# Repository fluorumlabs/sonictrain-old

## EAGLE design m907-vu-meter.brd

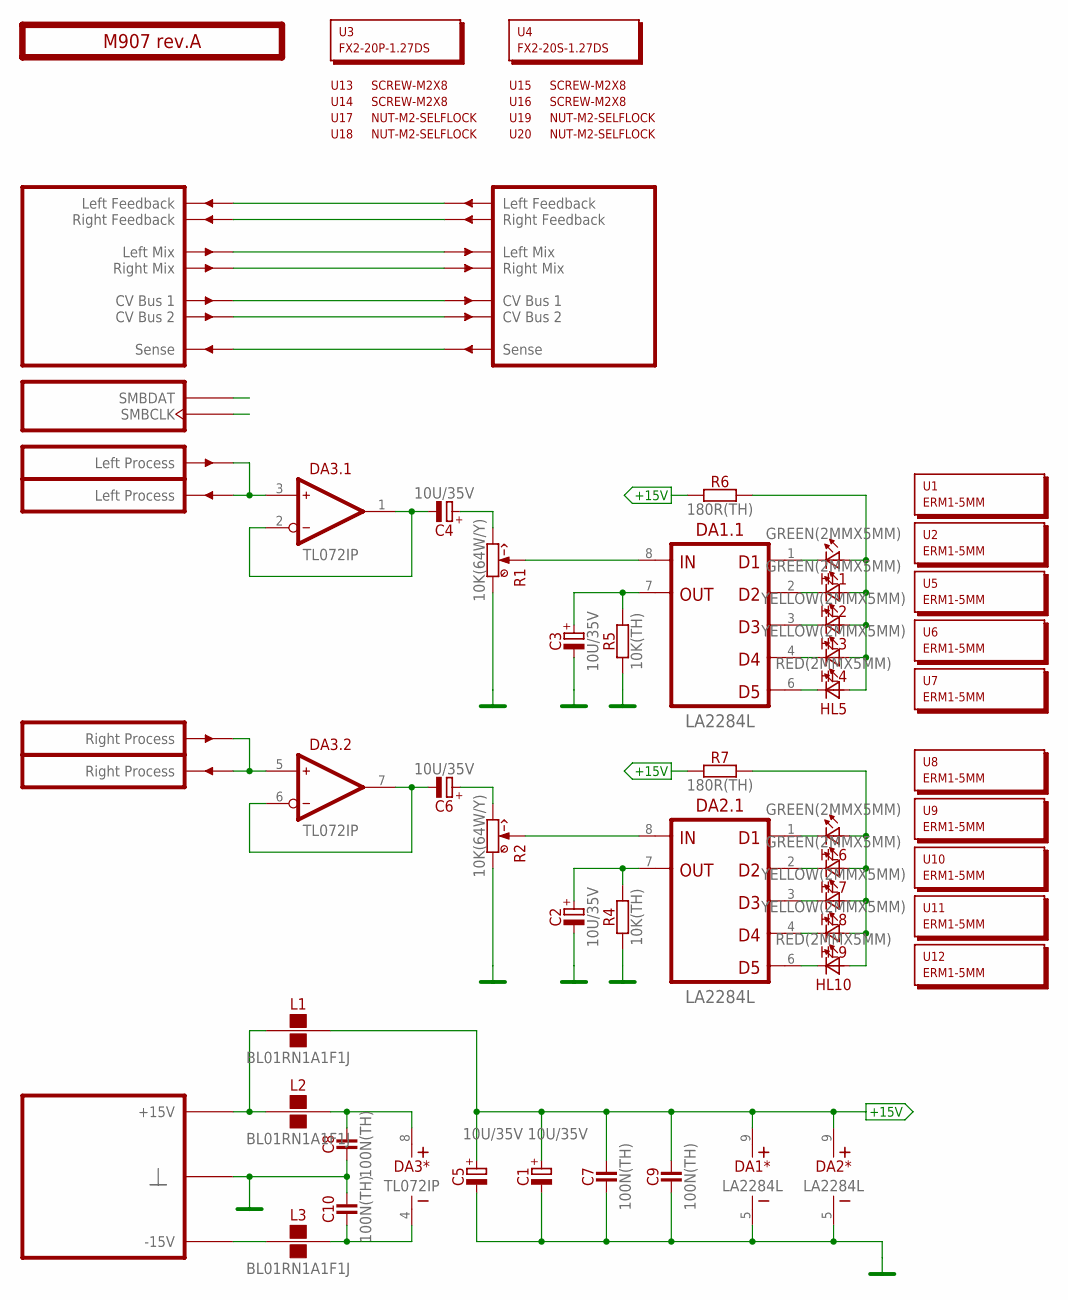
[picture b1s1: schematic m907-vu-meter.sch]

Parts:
C1, C2, C3, C4, C5, C6: 10U/35V; E2-5
C7, C8, C9, C10: 100N(TH); C050-024X044
DA1, DA2: LA2284L; SIL9
DA3: TL072IP; DIP-8
HL1, HL2, HL6, HL7: GREEN(2MMX5MM); LED2X5
HL3, HL4, HL8, HL9: YELLOW(2MMX5MM); LED2X5
HL5, HL10: RED(2MMX5MM); LED2X5
L1, L2, L3: BL01RN1A1F1J; BL01RN1A
PCB1: M907 rev.A; ST2-BOARD-26
R1, R2: 10K(64W/Y); 64W
R4, R5: 10K(TH); R-0207/10
R6, R7: 180R(TH); R-0207/10
U1, U2, U5, U6, U7, U8, U9, U10, U11, U12: ERM1-5MM; EMPTY
U3: FX2-20P-1.27DS; EMPTY
U4: FX2-20S-1.27DS; EMPTY
U13, U14, U15, U16: SCREW-M2X8; EMPTY
U17, U18, U19, U20: NUT-M2-SELFLOCK; EMPTY

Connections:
+15V: C1.+, C5.+, C7.2, C9.2, DA1.9 (V+), DA2.9 (V+), L1.2, R6.1, R7.1
GND: C1.-, C2.-, C3.-, C5.-, C7.1, C8.1, C9.1, C10.2, DA1.5 (V-), DA2.5 (V-), PCB1.B4 (GND), PCB1.B4' (GND), PCB1.B5 (GND), PCB1.B5' (GND), PCB1.B6 (GND), PCB1.B6' (GND), PCB1.B7 (GND), PCB1.B7' (GND), PCB1.B8 (GND), PCB1.B8' (GND), R1.1 (CCW), R2.1 (CCW), R4.1, R5.1
LMIX: PCB1.ALMIX (LMIX), PCB1.ALMIX' (LMIX')
unnamed: L1.1, L2.1, PCB1.A+15 (P+15V), PCB1.A+15' (P+15V), PCB1.B+15 (P+15V), PCB1.B+15' (P+15V)
unnamed: PCB1.ALFBK (LFBK), PCB1.ALFBK' (LFBK')
unnamed: DA2.8 (IN), R2.S (W), R2.S@1 (W)
unnamed: PCB1.ARFBK (RFBK), PCB1.ARFBK' (RFBK')
unnamed: DA1.8 (IN), R1.S (W), R1.S@1 (W)
unnamed: C3.+, DA1.7 (OUT), R5.2
unnamed: C2.+, DA2.7 (OUT), R4.2
unnamed: HL1.A, HL2.A, HL3.A, HL4.A, HL5.A, R6.2
unnamed: DA1.1 (D1), HL1.K (C)
unnamed: DA1.2 (D2), HL2.K (C)
unnamed: DA1.3 (D3), HL3.K (C)
unnamed: DA1.4 (D4), HL4.K (C)
unnamed: DA1.6 (D5), HL5.K (C)
unnamed: HL6.A, HL7.A, HL8.A, HL9.A, HL10.A, R7.2
unnamed: DA2.1 (D1), HL6.K (C)
unnamed: PCB1.BSENSE (SENSE), PCB1.BSENSE' (SENSE')
unnamed: DA2.2 (D2), HL7.K (C)
unnamed: DA2.3 (D3), HL8.K (C)
unnamed: DA2.4 (D4), HL9.K (C)
unnamed: DA2.6 (D5), HL10.K (C)
unnamed: C4.+, R1.3 (CW)
unnamed: C6.+, R2.3 (CW)
unnamed: DA3.3 (IN+), PCB1.BINL (INL), PCB1.BOUTL' (OUTL)
unnamed: DA3.5 (IN+), PCB1.BINR (INR), PCB1.BOUTR' (OUTR)
unnamed: L3.1, PCB1.A-15 (P-15V), PCB1.A-15' (P-15V), PCB1.B-15 (P-15V), PCB1.B-15' (P-15V)
unnamed: C8.2, DA3.8 (V+), L2.2
unnamed: C10.1, DA3.4 (V-), L3.2
unnamed: C4.-, DA3.1 (OUT), DA3.2 (IN-)
unnamed: C6.-, DA3.6 (IN-), DA3.7 (OUT)
unnamed: PCB1.ASMBDAT (SMBDAT), PCB1.ASMBDAT' (SMBDAT)
unnamed: PCB1.ACV1 (CV1), PCB1.ACV1' (CV1')
unnamed: PCB1.ACV2 (CV2), PCB1.ACV2' (CV2')
unnamed: PCB1.ASMBCLK (SMBCLK), PCB1.ASMBCLK' (SMBCLK)
RMIX: PCB1.ARMIX (RMIX), PCB1.ARMIX' (RMIX')

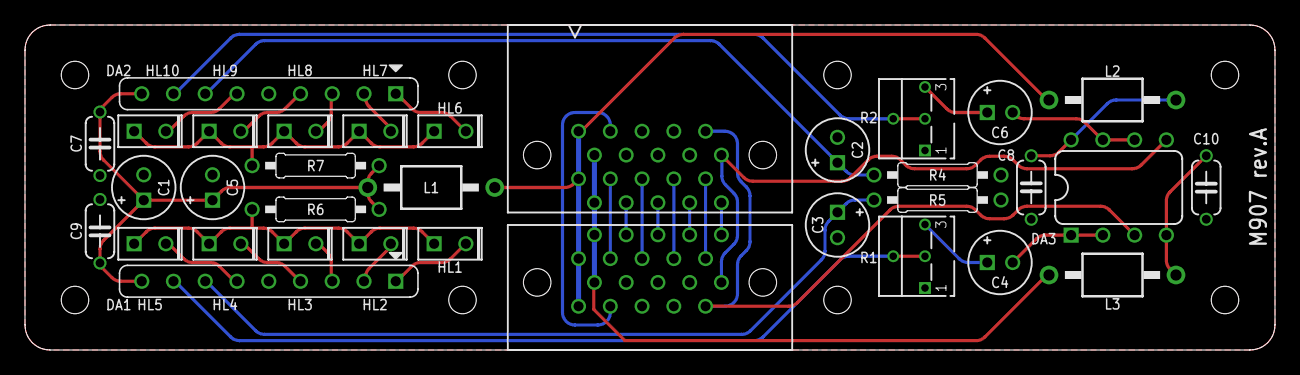
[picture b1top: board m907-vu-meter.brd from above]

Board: 2 copper layers, 100.0 x 26.0 mm, 53 parts (0 on the bottom side), 37 nets.

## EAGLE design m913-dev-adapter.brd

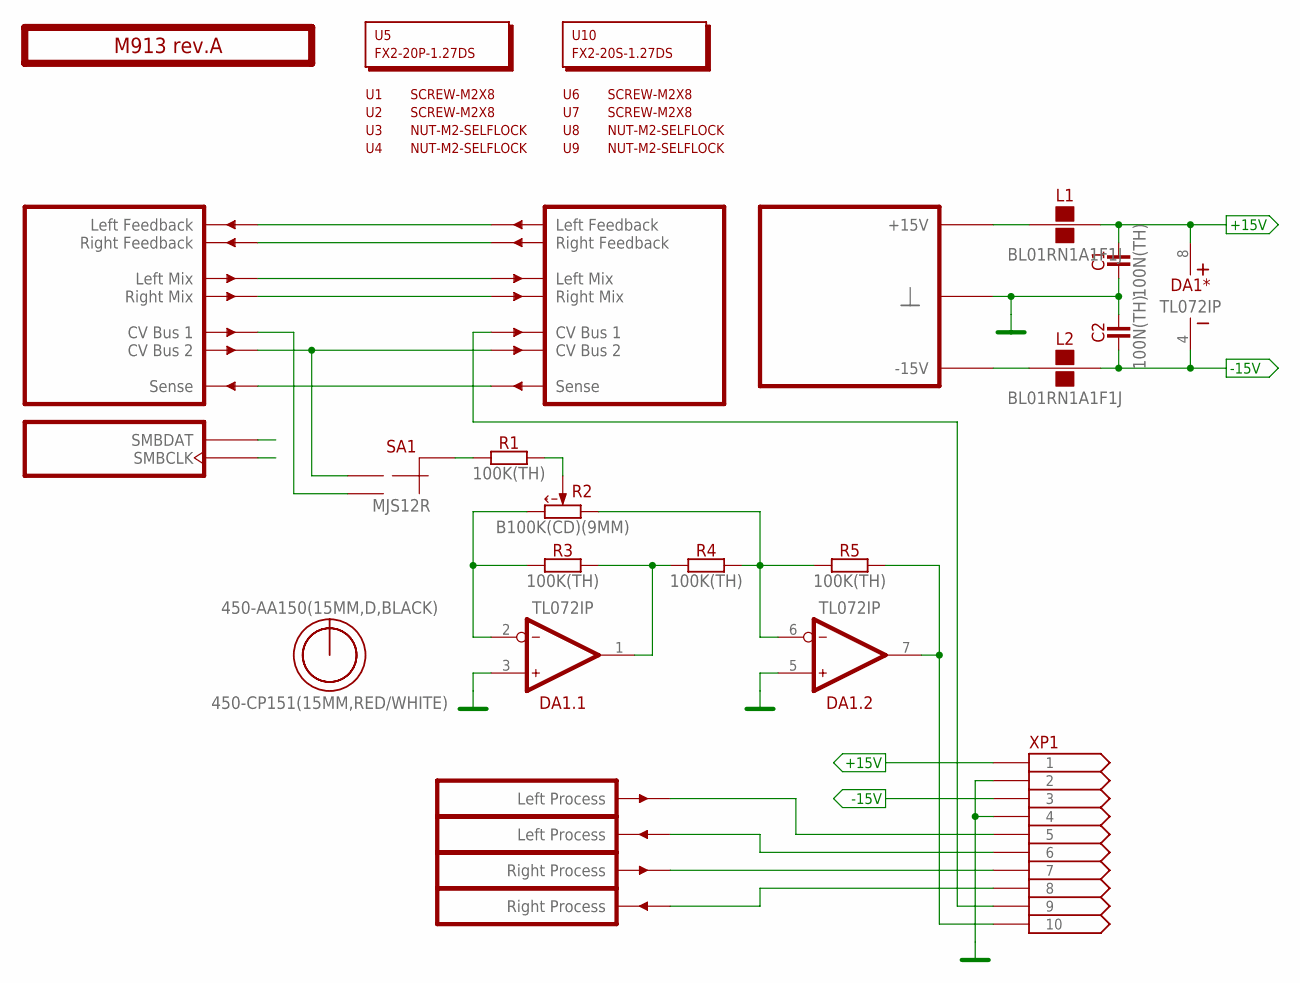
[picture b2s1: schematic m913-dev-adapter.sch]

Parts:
C1, C2: 100N(TH); C050-024X044
DA1: TL072IP; DIP-8
L1, L2: BL01RN1A1F1J; BL01RN1A
O1: 450-AA150(15MM,D,BLACK); EMPTY
O2: 450-CP151(15MM,RED/WHITE); EMPTY
PCB1: M913 rev.A; ST2-BOARD-26
R1, R3, R4, R5: 100K(TH); R-0207/10
R2: B100K(CD)(9MM); RV09-SINGLE
SA1: MJS12R; APEM-MJS12R
U1, U2, U6, U7: SCREW-M2X8; EMPTY
U3, U4, U8, U9: NUT-M2-SELFLOCK; EMPTY
U5: FX2-20P-1.27DS; EMPTY
U10: FX2-20S-1.27DS; EMPTY
XP1: CONN-10-IDC; ML10

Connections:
+15V: C1.2, DA1.8 (V+), L1.2, XP1.1
-15V: C2.1, DA1.4 (V-), L2.2, XP1.3
GND: C1.1, C2.2, DA1.3 (IN+), DA1.5 (IN+), PCB1.B4 (GND), PCB1.B4' (GND), PCB1.B5 (GND), PCB1.B5' (GND), PCB1.B6 (GND), PCB1.B6' (GND), PCB1.B7 (GND), PCB1.B7' (GND), PCB1.B8 (GND), PCB1.B8' (GND), XP1.2, XP1.4
LMIX: PCB1.ALMIX (LMIX), PCB1.ALMIX' (LMIX')
unnamed: L1.1, PCB1.A+15 (P+15V), PCB1.A+15' (P+15V), PCB1.B+15 (P+15V), PCB1.B+15' (P+15V)
unnamed: PCB1.ALFBK (LFBK), PCB1.ALFBK' (LFBK')
unnamed: R1.2, R2.2 (W)
unnamed: PCB1.ARFBK (RFBK), PCB1.ARFBK' (RFBK')
unnamed: DA1.2 (IN-), R2.3 (CW), R3.1
unnamed: DA1.1 (OUT), R3.2, R4.1
unnamed: DA1.6 (IN-), R2.1 (CCW), R4.2, R5.1
unnamed: DA1.7 (OUT), R5.2, XP1.10
unnamed: R1.1, SA1.C (CM)
unnamed: PCB1.BINL (INL), XP1.5
unnamed: PCB1.BOUTL' (OUTL), XP1.6
unnamed: PCB1.BINR (INR), XP1.7
unnamed: PCB1.BOUTR' (OUTR), XP1.8
unnamed: PCB1.ACV1' (CV1'), XP1.9
unnamed: PCB1.ACV1 (CV1), SA1.NO (2)
unnamed: PCB1.BSENSE (SENSE), PCB1.BSENSE' (SENSE')
unnamed: L2.1, PCB1.A-15 (P-15V), PCB1.A-15' (P-15V), PCB1.B-15 (P-15V), PCB1.B-15' (P-15V)
unnamed: PCB1.ASMBDAT (SMBDAT), PCB1.ASMBDAT' (SMBDAT)
unnamed: PCB1.ACV2 (CV2), PCB1.ACV2' (CV2'), SA1.NC (1)
unnamed: PCB1.ASMBCLK (SMBCLK), PCB1.ASMBCLK' (SMBCLK)
RMIX: PCB1.ARMIX (RMIX), PCB1.ARMIX' (RMIX')

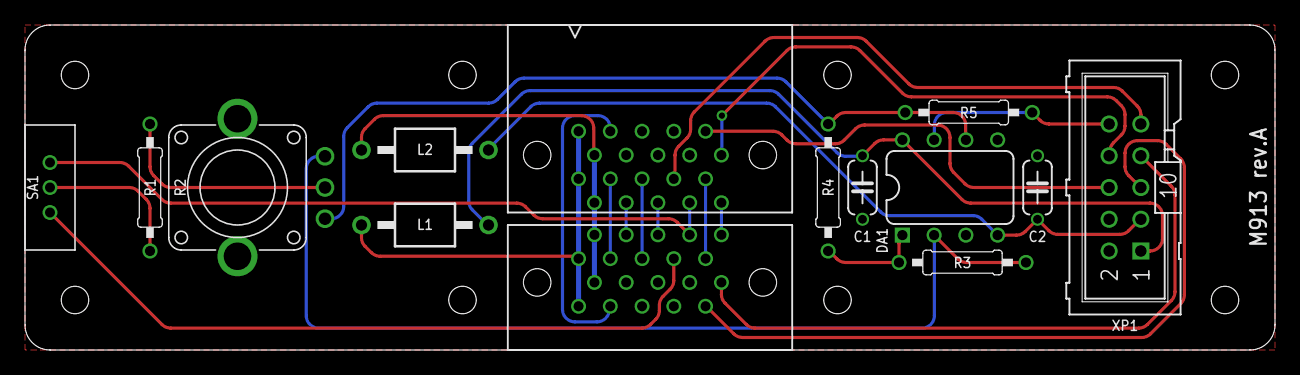
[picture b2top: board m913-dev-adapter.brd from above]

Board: 2 copper layers, 100.0 x 26.0 mm, 25 parts (0 on the bottom side), 25 nets.

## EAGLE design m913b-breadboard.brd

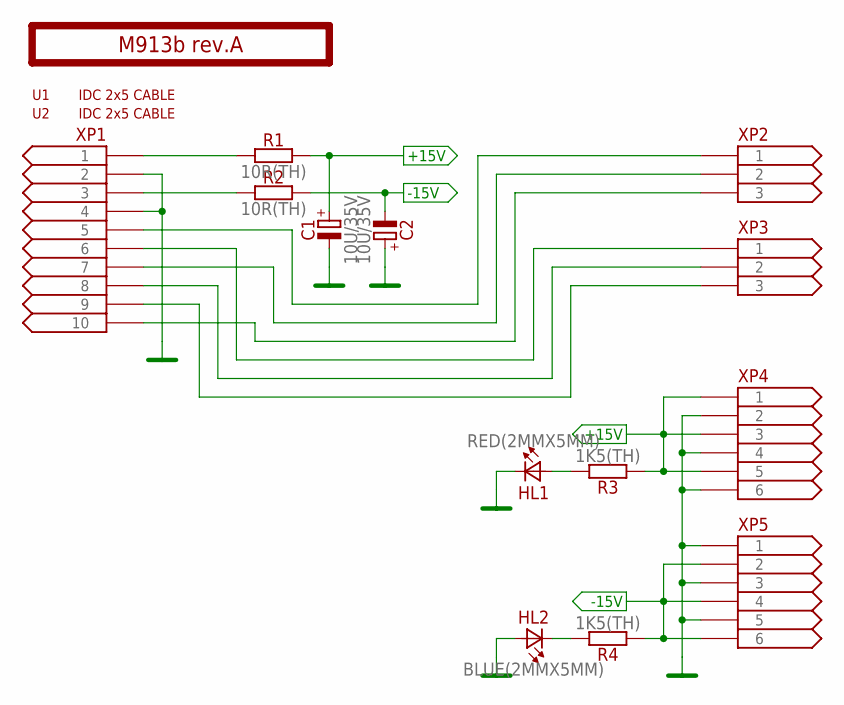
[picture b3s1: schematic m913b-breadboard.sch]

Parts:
C1, C2: 10U/35V; E2-5
HL1: RED(2MMX5MM); LED2X5
HL2: BLUE(2MMX5MM); LED2X5
PCB1: M913b rev.A; EMPTY
R1, R2: 10R(TH); R-0207/10
R3, R4: 1K5(TH); R-0207/10
U1, U2: IDC 2x5 CABLE; EMPTY
XP1: CONN-10-IDC; ML10
XP2, XP3: CONN-3-NORMAL; MA03-1
XP4, XP5: CONN-6-NORMAL; MA03-2

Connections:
+15V: C1.+, R1.2, R3.1, XP4.1, XP4.3, XP4.5
-15V: C2.-, R2.2, R4.1, XP5.2, XP5.4, XP5.6
GND: C1.-, C2.+, HL1.K (C), HL2.A, XP1.2, XP1.4, XP4.2, XP4.4, XP4.6, XP5.1, XP5.3, XP5.5
unnamed: HL1.A, R3.2
unnamed: R1.1, XP1.1
unnamed: R2.1, XP1.3
unnamed: HL2.K (C), R4.2
unnamed: XP1.5, XP2.1
unnamed: XP1.7, XP2.2
unnamed: XP1.10, XP2.3
unnamed: XP1.6, XP3.1
unnamed: XP1.8, XP3.2
unnamed: XP1.9, XP3.3

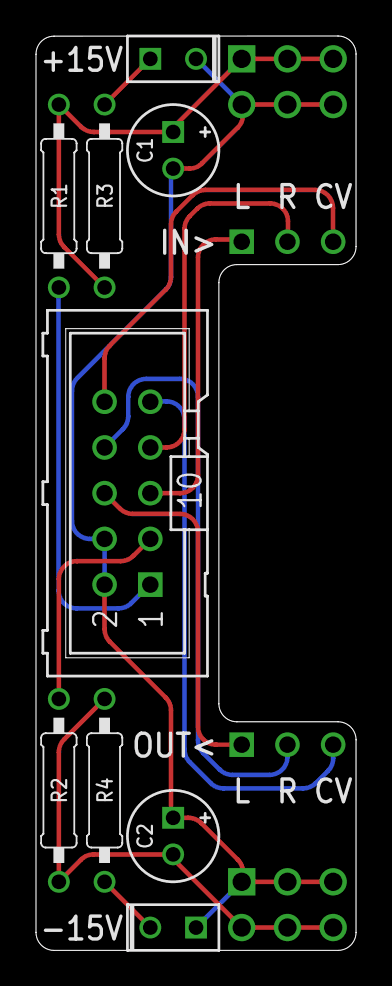
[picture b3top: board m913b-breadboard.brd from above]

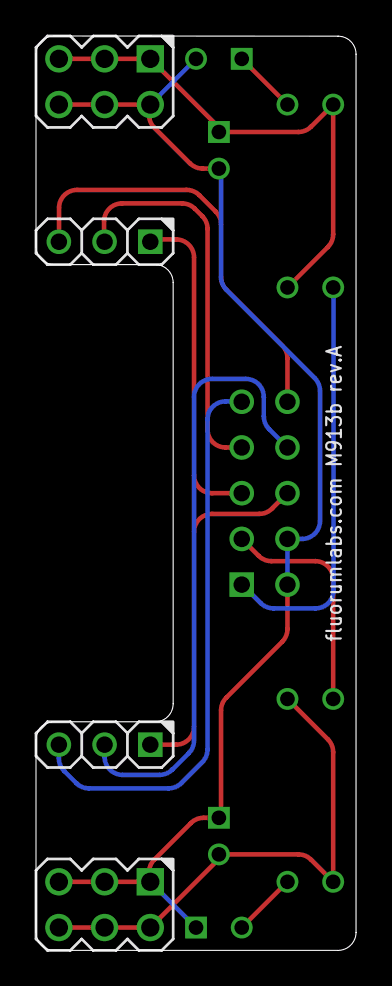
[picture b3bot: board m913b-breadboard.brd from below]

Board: 2 copper layers, 17.8 x 50.8 mm, 16 parts (4 on the bottom side), 13 nets.

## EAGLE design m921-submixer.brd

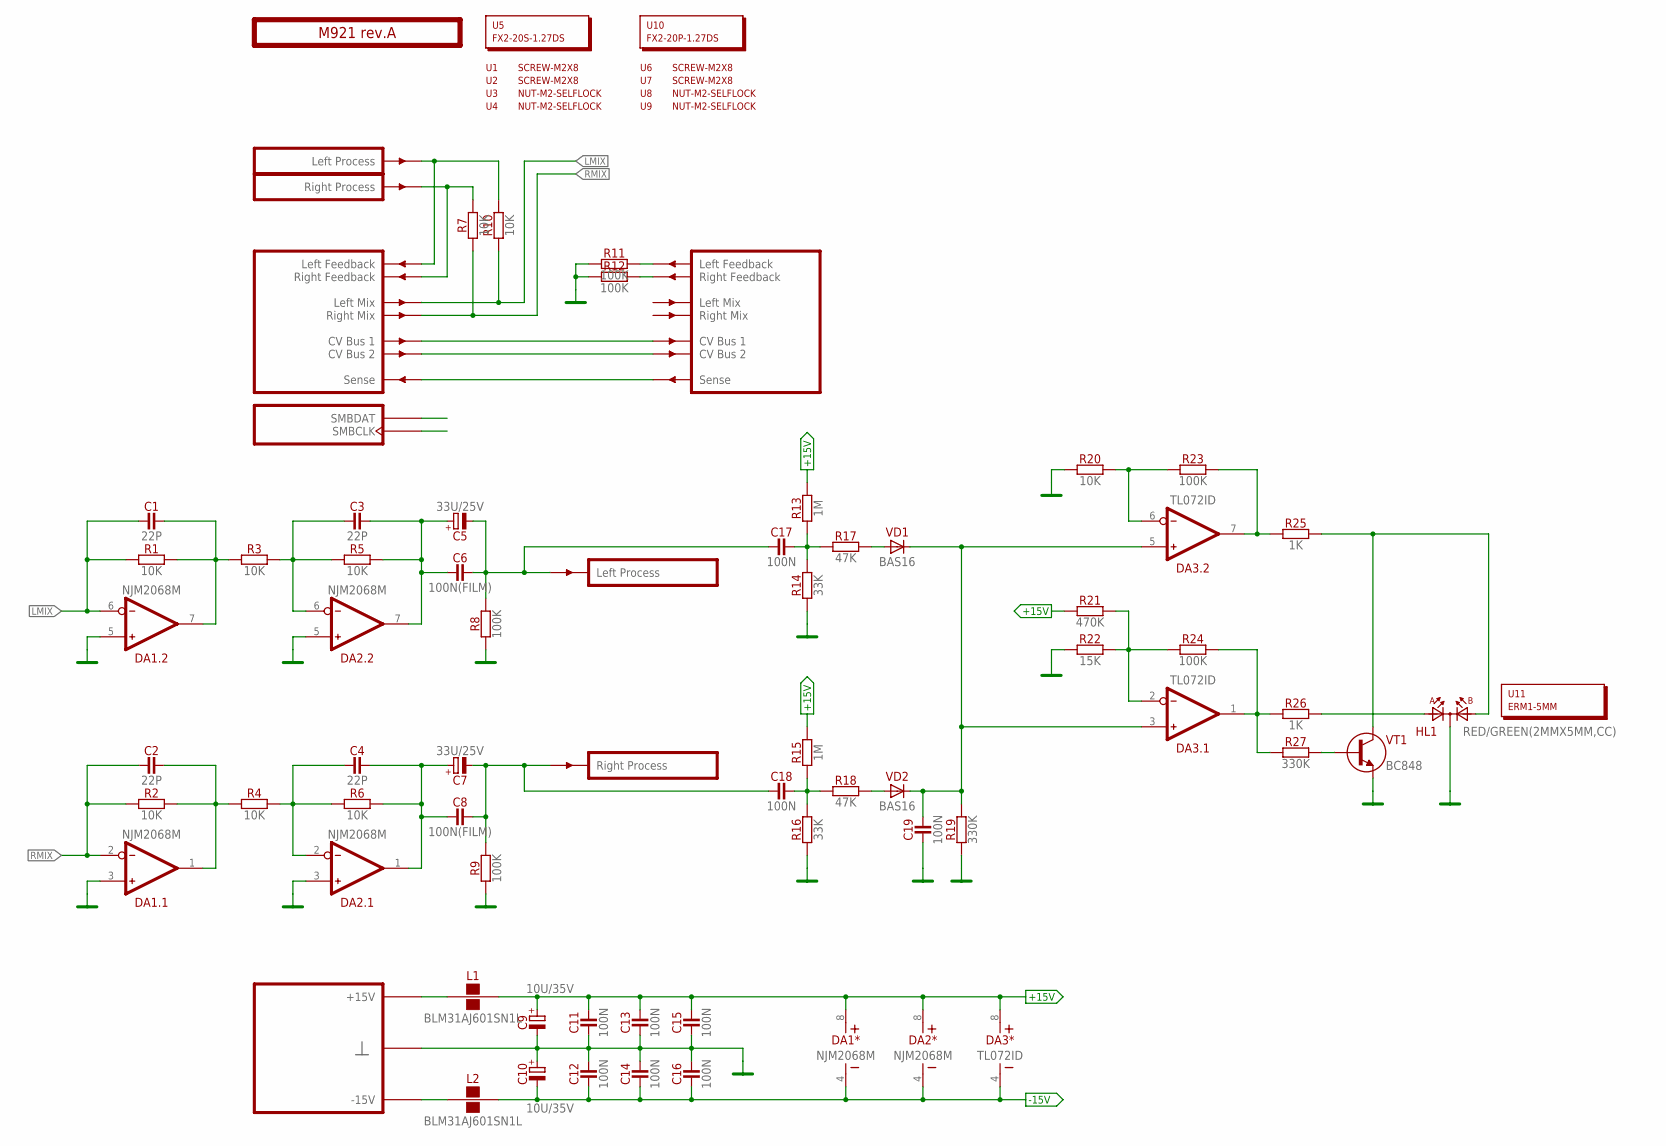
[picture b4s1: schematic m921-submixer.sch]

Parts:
C1, C2, C3, C4: 22P; C-0805
C5, C7: 33U/25V; E2,5-7
C6, C8: 100N(FILM); C050-025X075
C9, C10: 10U/35V; E2-5
C11, C12, C13, C14, C15, C16, C17, C18, C19: 100N; C-0805
DA1, DA2: NJM2068M; SO-8
DA3: TL072ID; SO-8
HL1: RED/GREEN(2MMX5MM,CC); LED2X5-3PIN
L1, L2: BLM31AJ601SN1L; 1206
PCB1: M921 rev.A; ST2-BOARD-26
R1, R2, R3, R4, R5, R6, R7, R10, R20: 10K; R-0805
R8, R9, R11, R12, R23, R24: 100K; R-0805
R13, R15: 1M; R-0805
R14, R16: 33K; R-0805
R17, R18: 47K; R-0805
R19, R27: 330K; R-0805
R21: 470K; R-0805
R22: 15K; R-0805
R25, R26: 1K; R-0805
U1, U2, U6, U7: SCREW-M2X8; EMPTY
U3, U4, U8, U9: NUT-M2-SELFLOCK; EMPTY
U5: FX2-20S-1.27DS; EMPTY
U10: FX2-20P-1.27DS; EMPTY
U11: ERM1-5MM; EMPTY
VD1, VD2: BAS16; SOT23
VT1: BC848; SOT23

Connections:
+15V: C9.+, C11.2, C13.2, C15.2, DA1.8 (V+), DA2.8 (V+), DA3.8 (V+), L1.2, R13.2, R15.2, R21.1
-15V: C10.-, C12.1, C14.1, C16.1, DA1.4 (V-), DA2.4 (V-), DA3.4 (V-), L2.2
GND: C9.-, C10.+, C11.1, C12.2, C13.1, C14.2, C15.1, C16.2, C19.1, DA1.3 (IN+), DA1.5 (IN+), DA2.3 (IN+), DA2.5 (IN+), HL1.K, PCB1.B4 (GND), PCB1.B4' (GND), PCB1.B5 (GND), PCB1.B5' (GND), PCB1.B6 (GND), PCB1.B6' (GND), PCB1.B7 (GND), PCB1.B7' (GND), PCB1.B8 (GND), PCB1.B8' (GND), R8.1, R9.1, R11.1, R12.1, R14.1, R16.1, R19.1, R20.1, R22.1, VT1.2 (E)
LMIX: C1.1, DA1.6 (IN-), PCB1.ALMIX (LMIX), R1.1, R10.1
unnamed: L1.1, PCB1.A+15 (P+15V), PCB1.A+15' (P+15V), PCB1.B+15 (P+15V), PCB1.B+15' (P+15V)
unnamed: PCB1.BSENSE (SENSE), PCB1.BSENSE' (SENSE')
unnamed: PCB1.ACV2 (CV2), PCB1.ACV2' (CV2')
unnamed: L2.1, PCB1.A-15 (P-15V), PCB1.A-15' (P-15V), PCB1.B-15 (P-15V), PCB1.B-15' (P-15V)
unnamed: PCB1.ACV1 (CV1), PCB1.ACV1' (CV1')
unnamed: C1.2, DA1.7 (OUT), R1.2, R3.1
unnamed: C2.2, DA1.1 (OUT), R2.2, R4.1
unnamed: DA3.6 (IN-), R20.2, R23.1
unnamed: DA3.7 (OUT), R23.2, R25.1
unnamed: C7.-, C8.2, C18.1, PCB1.BOUTR' (OUTR), R9.2
unnamed: C5.-, C6.2, C17.1, PCB1.BOUTL' (OUTL), R8.2
unnamed: C17.2, R13.1, R14.2, R17.1
unnamed: R17.2, VD1.1 (A)
unnamed: C18.2, R15.1, R16.2, R18.1
unnamed: R18.2, VD2.1 (A)
unnamed: C19.2, DA3.3 (IN+), DA3.5 (IN+), R19.2, VD1.2 (C), VD2.2 (C)
unnamed: PCB1.ALFBK' (LFBK'), R11.2
unnamed: PCB1.ARFBK' (RFBK'), R12.2
unnamed: HL1.A2, R25.2, VT1.3 (C)
unnamed: DA3.2 (IN-), R21.2, R22.2, R24.1
unnamed: DA3.1 (OUT), R24.2, R26.1, R27.1
unnamed: R27.2, VT1.1 (B)
unnamed: HL1.A1, R26.2
unnamed: PCB1.ASMBDAT (SMBDAT), PCB1.ASMBDAT' (SMBDAT)
unnamed: PCB1.ARFBK (RFBK), PCB1.BINR (INR), R7.2
unnamed: PCB1.ALFBK (LFBK), PCB1.BINL (INL), R10.2
unnamed: PCB1.ASMBCLK (SMBCLK), PCB1.ASMBCLK' (SMBCLK)
unnamed: C3.1, DA2.6 (IN-), R3.2, R5.1
unnamed: C3.2, C5.+, C6.1, DA2.7 (OUT), R5.2
unnamed: C4.1, DA2.2 (IN-), R4.2, R6.1
unnamed: C4.2, C7.+, C8.1, DA2.1 (OUT), R6.2
RMIX: C2.1, DA1.2 (IN-), PCB1.ARMIX (RMIX), R2.1, R7.1

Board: 2 copper layers, 67 parts (0 on the bottom side), 36 nets, no tracks yet.
